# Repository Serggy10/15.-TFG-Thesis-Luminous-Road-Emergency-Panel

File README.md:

# Description
This folder contains my thesis memory of a luminous road emergency panel, which can be controlled by a touchscreen and wirelessly. It also contains all the code in an appendices folder. An abstract of the memory is the following:

This document describes the process of improving a road emergency panel which was
developed previously in the electronic technology department in the university of
Valladolid. This project arises from the limitations of the previous panel with the
objective of generate clearly message to the road users.
The main characteristics of the project are taken from a market study from which the
selected components will be selected to meet certain objectives of this project.
In this project a microcontroller will be programmed so it can control the emergency
panel according to a user interface on a touch screen. Additionally, an Android
application will be developed to control the device remotely using Bluetooth. All these
systems will be protected by some 3D printed designs.
Keywords
LED panel, ESP32, touch screen, Bluetooth, Android

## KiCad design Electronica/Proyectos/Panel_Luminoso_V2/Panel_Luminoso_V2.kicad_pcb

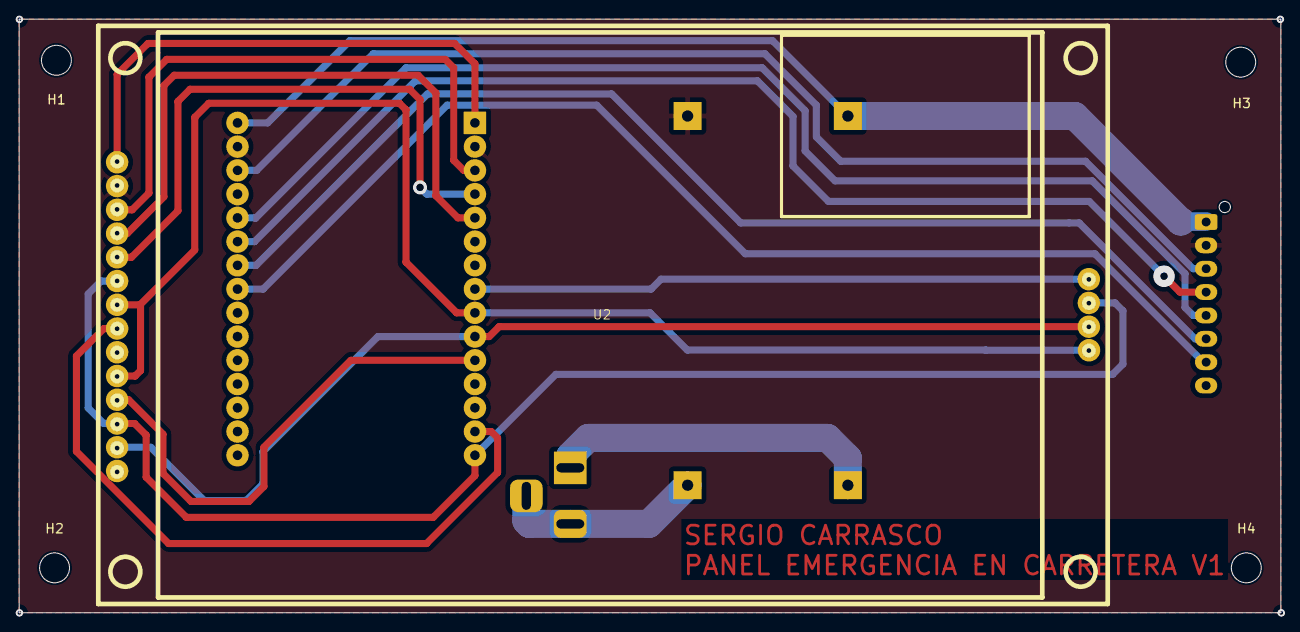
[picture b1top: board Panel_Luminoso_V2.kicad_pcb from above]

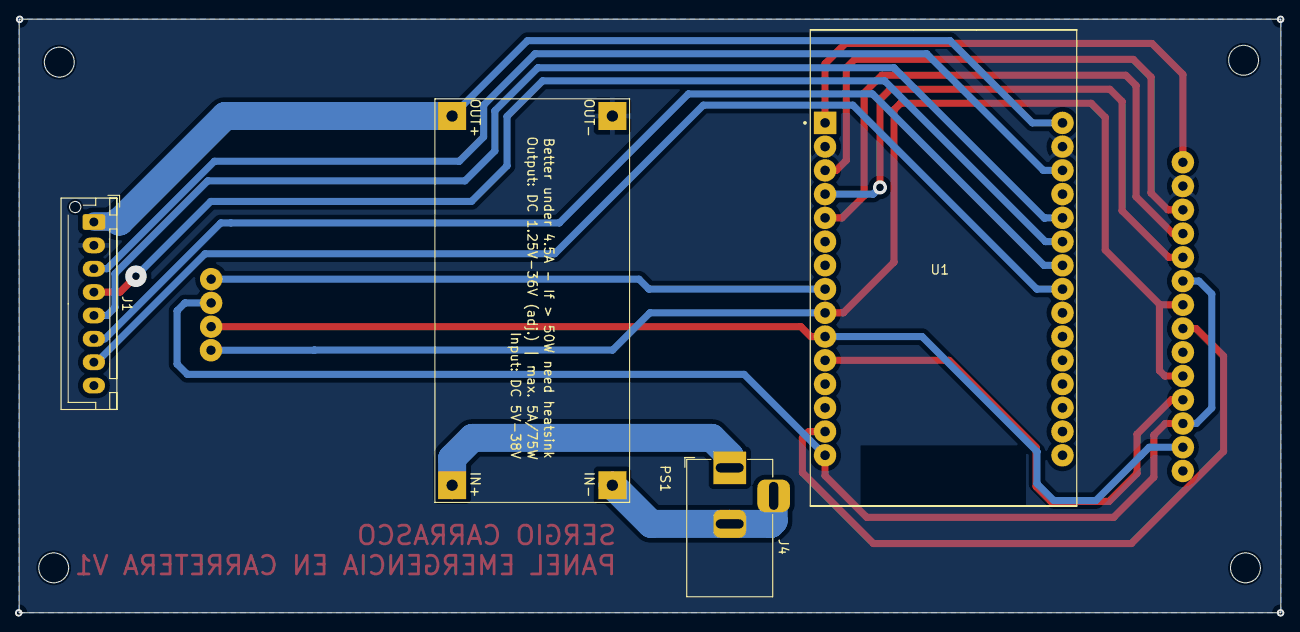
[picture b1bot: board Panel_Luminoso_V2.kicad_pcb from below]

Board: 2 copper layers, 135.0 x 63.5 mm, 9 parts (4 on the bottom side), 19 nets.

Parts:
H1, H2, H3, H4: MountingHole; MountingHole_3.2mm_M3
J1: Screw_Terminal_01x08; JST_XH_B8B-XH-AM_1x08_P2.50mm_Vertical
J4: BarrelJack; BarrelJack_Horizontal
PS1: XL4005_DC-DC; XL4005_DC-DC_SinAgujeros
U1: ESP32-DEVKIT-V1; MODULE_ESP32_DEVKIT_V1_SinAgujeros
U2: ILI9488

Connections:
+5V: J1.1, PS1.3 (OUT+), U1.30 (VIN)
+12V: J4.1, PS1.1 (IN+)
/BACK_LIGHT: U1.14 (D22), U2.8 (BL)
/CLK SD/TFT/TOUCH: U1.9 (D18), U2.7 (SCK), U2.10 (TCK), U2.18 (CLK)
/CS SD: U1.8 (D5), U2.15 (SCS)
/CS TFT: U1.3 (D15), U2.3 (CS)
/CS TOUCH: U1.11 (D21), U2.11 (TCS)
/D/C TFT: U1.4 (D2), U2.5 (D/C)
/LDR: J1.7, U1.23 (D25)
/LED CLK PIN: J1.5, U1.26 (D14)
/LED CS PIN: J1.4, U1.25 (D27)
/LED DATA PIN: J1.3, U1.28 (D13)
/MISO SD/TFT/TOUCH: U1.10 (D19), U2.13 (TD0), U2.17 (SDO)
/MOSI SD/TFT/TOUCH: U1.15 (D23), U2.6 (SDI), U2.12 (TDI), U2.16 (SDI)
/RST TFT: U1.5 (D4), U2.4 (RST)
/SERVO: J1.6, U1.24 (D26)
GND: J4.2, J4.3, PS1.2 (IN-)
GND1: J1.2, PS1.4 (OUT-), U1.2 (GND), U1.29 (GND), U2.2 (GND)
VCC: U1.1 (3V3), U2.1 (VDD)

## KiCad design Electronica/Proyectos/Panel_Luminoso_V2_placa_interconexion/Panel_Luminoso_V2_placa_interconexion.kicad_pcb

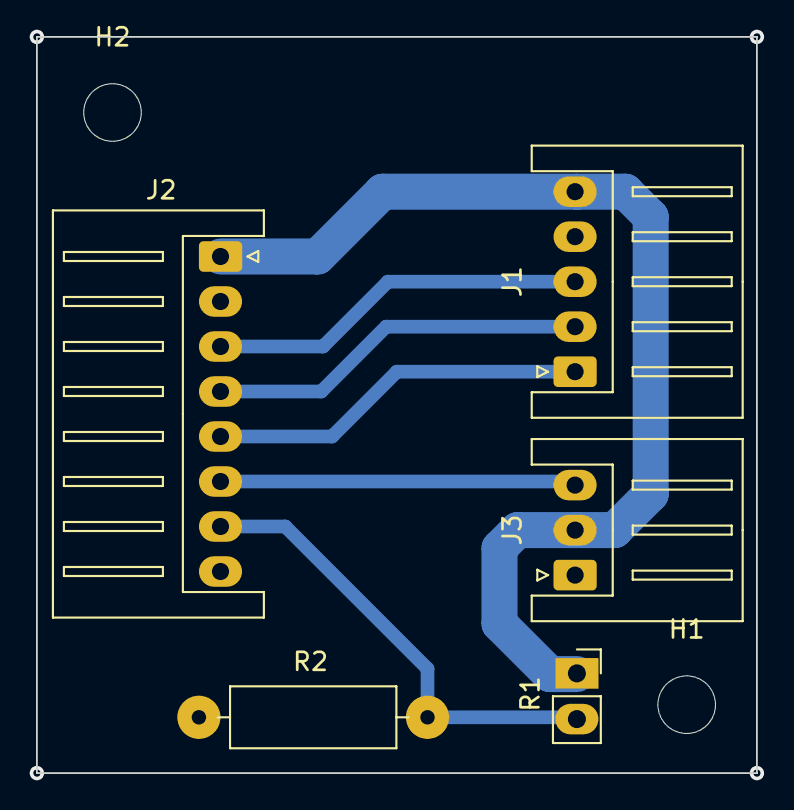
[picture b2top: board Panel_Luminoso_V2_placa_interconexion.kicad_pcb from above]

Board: 2 copper layers, 40.0 x 40.9 mm, 7 parts (0 on the bottom side), 7 nets.

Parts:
H1, H2: MountingHole; MountingHole_3.2mm_M3
J1: Screw_Terminal_01x05; JST_XH_S5B-XH-A_1x05_P2.50mm_Horizontal
J2: Screw_Terminal_01x08; JST_XH_S8B-XH-A_1x08_P2.50mm_Horizontal
J3: Screw_Terminal_01x03; JST_XH_S3B-XH-A_1x03_P2.50mm_Horizontal
R1: M9960; PinSocket_1x02_P2.54mm_Vertical
R2: 10K; R_Axial_DIN0309_L9.0mm_D3.2mm_P12.70mm_Horizontal

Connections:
/5V_: J1.5, J2.1, J3.2, R1.1
/GND_: J1.4, J2.2, J3.1, R2.2
/LDR_: J2.7, R1.2, R2.1
/LED CLK PIN_: J1.1, J2.5
/LED CS PIN_: J1.2, J2.4
/LED DATA PIN_: J1.3, J2.3
/SERVO_: J2.6, J3.3

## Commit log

2025-03-06 Initial commit.
